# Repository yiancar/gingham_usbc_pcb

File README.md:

Gingham-USBC
================

This ANSI/ISO keyboard kit is made using ONLY through hole components and inspired by the [Plaid](https://github.com/hsgw/plaid).

Atmega328p with VUSB on [QMK firmware](https://github.com/qmk/qmk_firmware).

To alter the pcb use KiCAD V5.0 or newer as it already contains most of the libraries. The additional libraries are provided.

License
===========

This project is licensed under the [Creative Commons Attribution-NonCommercial 4.0 International License](https://creativecommons.org/licenses/by-nc/4.0/).

If you have remixed, adapted or build upon this work and wish to remove the non-commercial clause for your own project please contact me at https://www.yiancar-designs.com. Your request is more than likely to be granted. The non-commercial part of the license is intended to avoid direct copies of the work to be sold for commercial gain by third parties.

The USB4085-GF-A footprint, symbol and 3D model are licensed under [Attribution-ShareAlike 4.0 International](https://creativecommons.org/licenses/by-sa/4.0/). Originally created by [SnapEDA](https://snapeda.com). The footprint has been modified to increase the hole size of the shield pads.

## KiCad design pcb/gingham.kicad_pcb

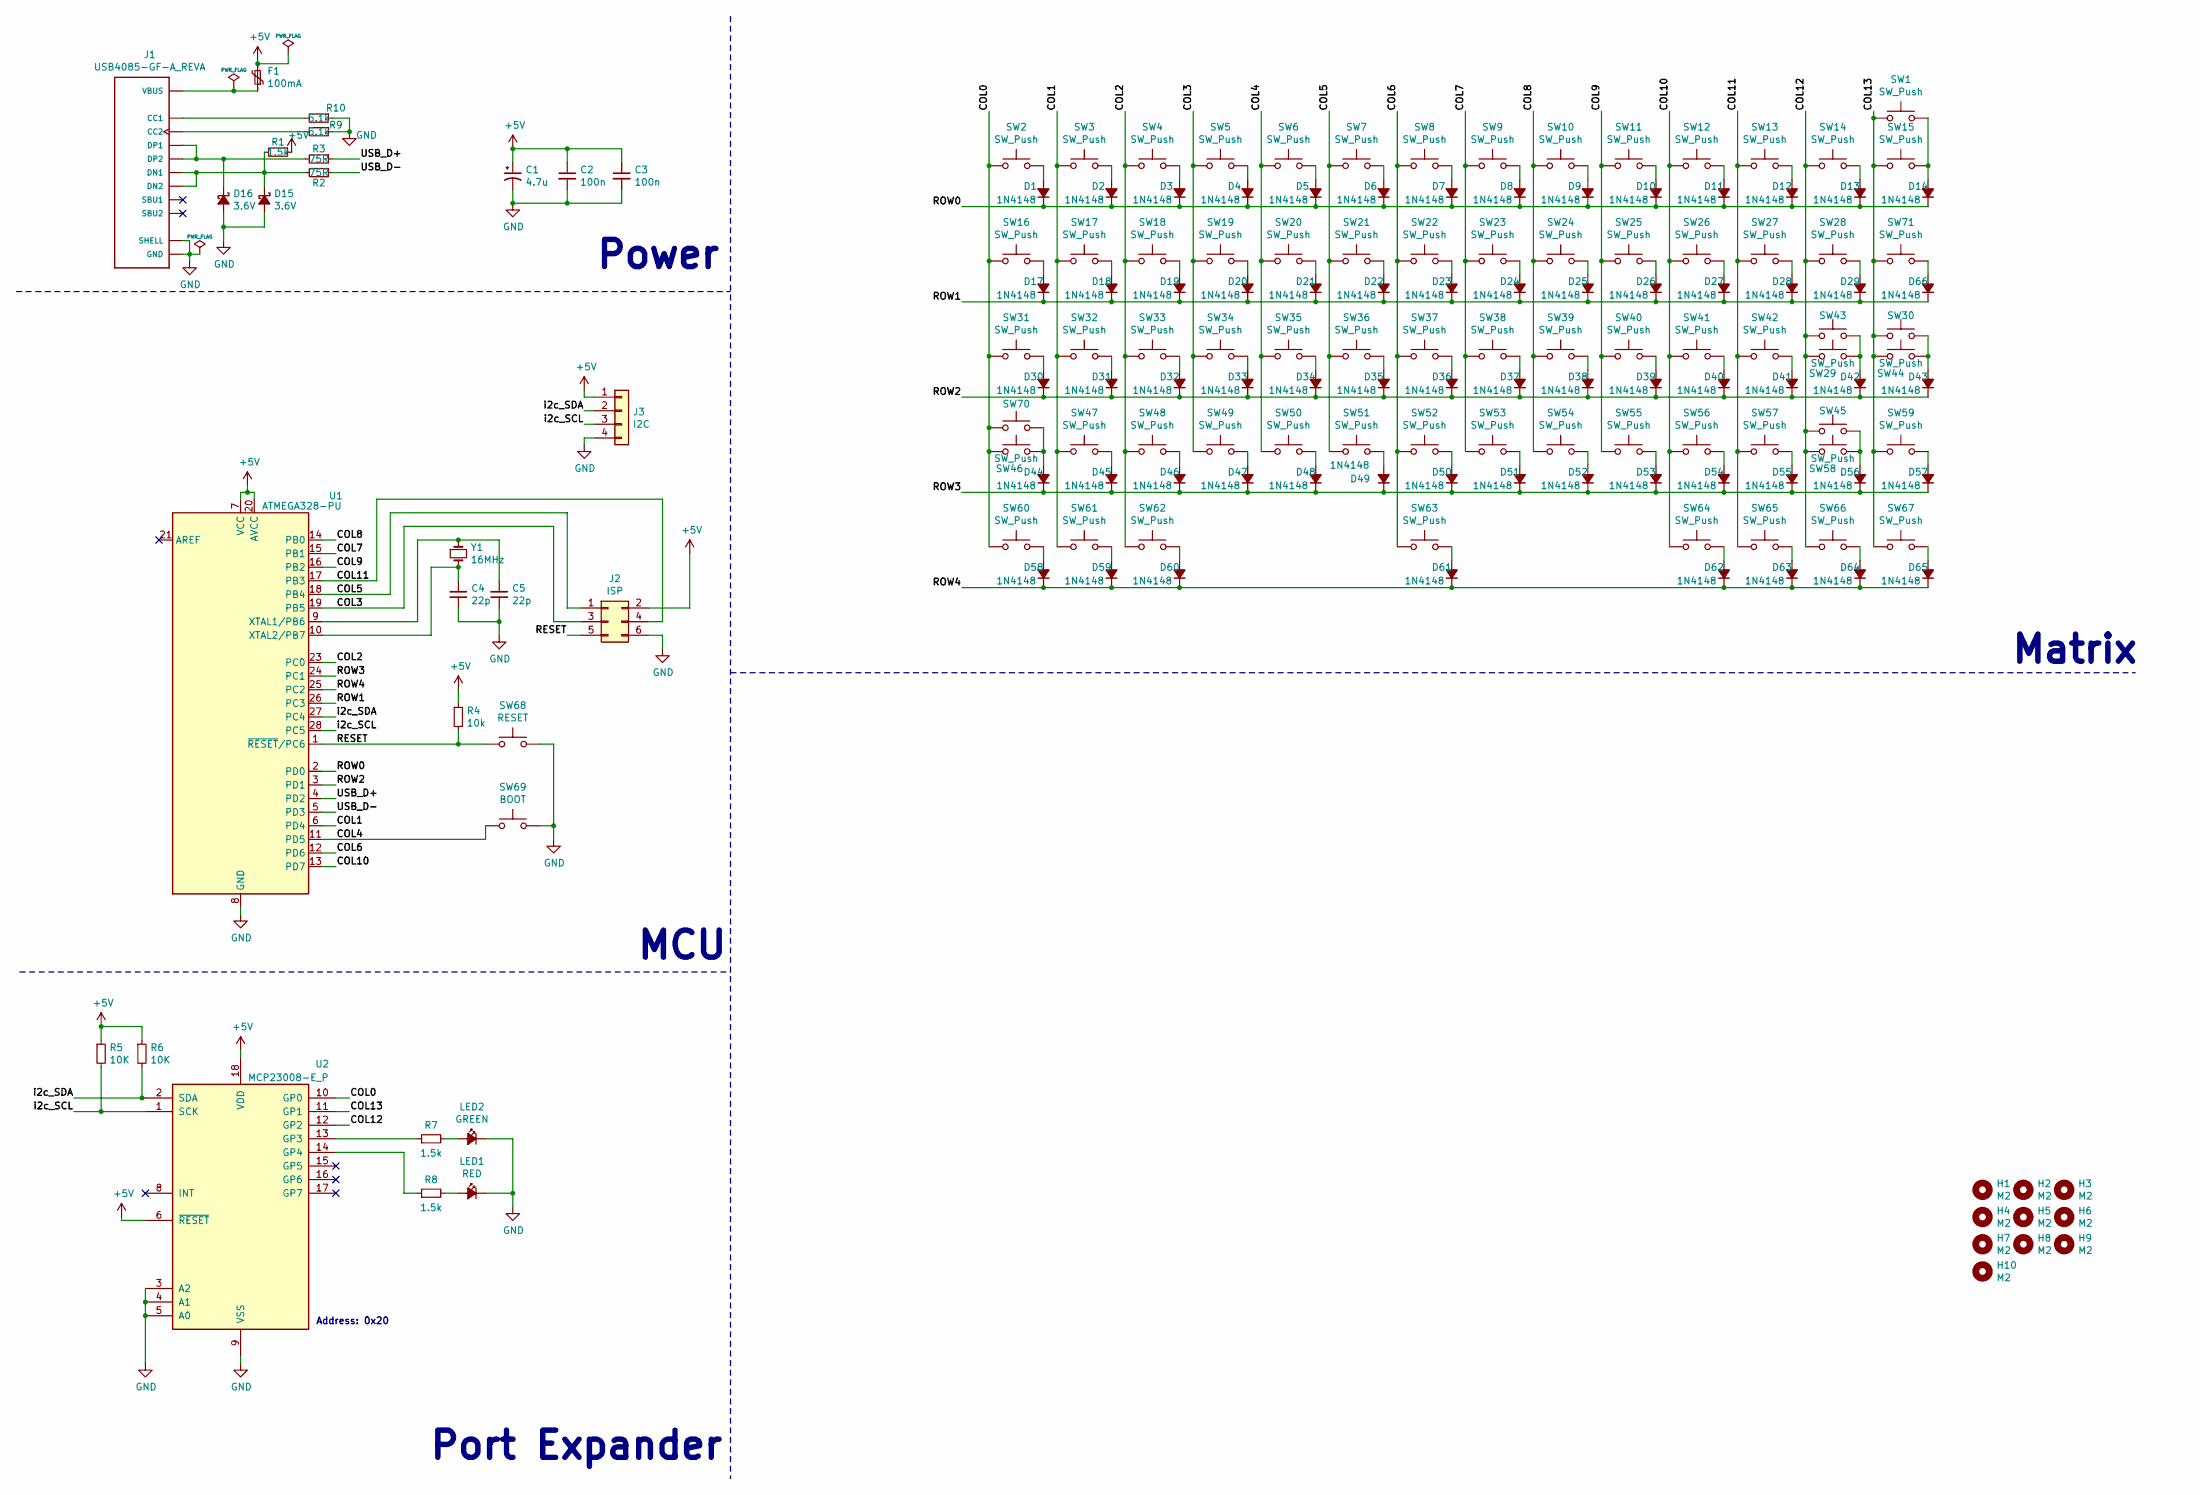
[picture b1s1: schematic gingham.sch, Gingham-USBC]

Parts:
C1: 4.7u; CP_Radial_D4.0mm_P1.50mm
C2, C3: 100n; C_Disc_D4.3mm_W1.9mm_P5.00mm
C4, C5: 22p; C_Disc_D4.3mm_W1.9mm_P5.00mm
D1, D2, D3, D4, D5, D6, D7, D8, D9, D10, D11, D12, D13, D14, D17, D18, D19, D20, D21, D22, D23, D24, D25, D26, D27, D28, D29, D30, D31, D32, D33, D34, D35, D36, D37, D38, D39, D40, D41, D42, D43, D44, D45, D46, D47, D48, D49, D50, D51, D52, D53, D54, D55, D56, D57, D58, D59, D60, D61, D62, D63, D64, D65, D66: 1N4148; D_DO-35_SOD27_P7.62mm_Horizontal
D15, D16: 3.6V; D_DO-35_SOD27_P7.62mm_Horizontal
F1: 100mA; C_Disc_D5.0mm_W2.5mm_P5.00mm
H1, H2, H3, H4, H5, H6, H7, H8, H9, H10: M2; MountingHole_2.2mm_M2_DIN965_Pad
J1: USB4085-GF-A_REVA; GCT_USB4085-GF-A_REVA
J2: ISP; PinHeader_2x03_P2.54mm_Vertical
J3: I2C; PinHeader_1x04_P2.54mm_Vertical
LED1: RED; LED_D3.0mm_Clear
LED2: GREEN; LED_D3.0mm_Clear
R1, R7, R8: 1.5k; R_Axial_DIN0204_L3.6mm_D1.6mm_P5.08mm_Horizontal
R2, R3: 75R; R_Axial_DIN0204_L3.6mm_D1.6mm_P5.08mm_Horizontal
R4: 10k; R_Axial_DIN0204_L3.6mm_D1.6mm_P5.08mm_Horizontal
R5, R6: 10K; R_Axial_DIN0204_L3.6mm_D1.6mm_P5.08mm_Horizontal
R9, R10: 5.1k; R_Axial_DIN0204_L3.6mm_D1.6mm_P5.08mm_Horizontal
SW1: SW_Push; MX-2U-NoLED
SW2, SW3, SW4, SW5, SW6, SW7, SW8, SW9, SW10, SW11, SW12, SW13, SW14, SW15, SW17, SW18, SW19, SW20, SW21, SW22, SW23, SW24, SW25, SW26, SW27, SW28, SW29, SW32, SW33, SW34, SW35, SW36, SW37, SW38, SW39, SW40, SW41, SW42, SW47, SW48, SW49, SW50, SW51, SW52, SW53, SW54, SW55, SW56, SW57, SW59, SW71: SW_Push; MX-1U-NoLED
SW16, SW43: SW_Push; MX-1.5U-NoLED
SW30: SW_Push; MX-ISO-ReversedStabilizers
SW31, SW45: SW_Push; MX-1.75U-NoLED
SW44, SW46: SW_Push; MX-2.25U-NoLED
SW58: SW_Push; MX-2.75U-NoLED
SW60, SW61, SW62, SW64, SW65, SW66, SW67, SW70: SW_Push; MX-1.25U-NoLED
SW63: SW_Push; MX-6.25U-ReversedStabilizers-NoLED
SW68: RESET; SW_PUSH_6mm
SW69: BOOT; SW_PUSH_6mm
U1: ATMEGA328-PU; DIP-28_W7.62mm
U2: MCP23008-E_P; DIP-18_W7.62mm
Y1: 16MHz; Crystal_HC49-4H_Vertical

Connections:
+5V: C1.1, C2.1, C3.1, F1.2, J2.2, J3.1, R1.1, R4.1, R5.1, R6.1, U1.7 (VCC), U1.20 (AVCC), U2.6 (~RESET~), U2.18 (VDD)
/COL0: SW2.2, SW16.2, SW31.2, SW46.2, SW60.2, SW70.2, U2.10 (GP0)
/COL1: SW3.2, SW17.2, SW32.2, SW47.2, SW61.2, U1.6 (PD4)
/COL2: SW4.2, SW18.2, SW33.2, SW48.2, SW62.2, U1.23 (PC0)
/COL3: J2.3, SW5.2, SW19.2, SW34.2, SW49.2, U1.19 (PB5)
/COL4: SW6.2, SW20.2, SW35.2, SW50.2, SW69.1, U1.11 (PD5)
/COL5: J2.1, SW7.2, SW21.2, SW36.2, SW51.2, U1.18 (PB4)
/COL6: SW8.2, SW22.2, SW37.2, SW52.2, SW63.2, U1.12 (PD6)
/COL7: SW9.2, SW23.2, SW38.2, SW53.2, U1.15 (PB1)
/COL8: SW10.2, SW24.2, SW39.2, SW54.2, U1.14 (PB0)
/COL9: SW11.2, SW25.2, SW40.2, SW55.2, U1.16 (PB2)
/COL10: SW12.2, SW26.2, SW41.2, SW56.2, SW64.2, U1.13 (PD7)
/COL11: J2.4, SW13.2, SW27.2, SW42.2, SW57.2, SW65.2, U1.17 (PB3)
/COL12: SW14.2, SW28.2, SW29.2, SW43.2, SW45.2, SW58.2, SW66.2, U2.12 (GP2)
/COL13: SW1.2, SW15.2, SW30.2, SW44.2, SW59.2, SW67.2, SW71.2, U2.11 (GP1)
/RESET: J2.5, R4.2, SW68.1, U1.1 (~RESET~/PC6)
/ROW0: D1.1 (K), D2.1 (K), D3.1 (K), D4.1 (K), D5.1 (K), D6.1 (K), D7.1 (K), D8.1 (K), D9.1 (K), D10.1 (K), D11.1 (K), D12.1 (K), D13.1 (K), D14.1 (K), U1.2 (PD0)
/ROW1: D17.1 (K), D18.1 (K), D19.1 (K), D20.1 (K), D21.1 (K), D22.1 (K), D23.1 (K), D24.1 (K), D25.1 (K), D26.1 (K), D27.1 (K), D28.1 (K), D29.1 (K), D66.1 (K), U1.26 (PC3)
/ROW2: D30.1 (K), D31.1 (K), D32.1 (K), D33.1 (K), D34.1 (K), D35.1 (K), D36.1 (K), D37.1 (K), D38.1 (K), D39.1 (K), D40.1 (K), D41.1 (K), D42.1 (K), D43.1 (K), U1.3 (PD1)
/ROW3: D44.1 (K), D45.1 (K), D46.1 (K), D47.1 (K), D48.1 (K), D49.1 (K), D50.1 (K), D51.1 (K), D52.1 (K), D53.1 (K), D54.1 (K), D55.1 (K), D56.1 (K), D57.1 (K), U1.24 (PC1)
/ROW4: D58.1 (K), D59.1 (K), D60.1 (K), D61.1 (K), D62.1 (K), D63.1 (K), D64.1 (K), D65.1 (K), U1.25 (PC2)
/USB_D+: R3.1, U1.4 (PD2)
/USB_D-: R2.1, U1.5 (PD3)
/i2c_SCL: J3.3, R5.2, U1.28 (PC5), U2.1 (SCK)
/i2c_SDA: J3.2, R6.2, U1.27 (PC4), U2.2 (SDA)
GND: C1.2, C2.2, C3.2, C4.2, C5.2, D15.2 (A), D16.2 (A), J1.A1 (GND), J1.A12 (GND), J1.B1 (GND), J1.B12 (GND), J1.P1 (SHELL), J1.P2 (SHELL), J1.P3 (SHELL), J1.P4 (SHELL), J2.6, J3.4, LED1.1 (K), LED2.1 (K), R9.1, R10.1, SW68.2, SW69.2, U1.8 (GND), U1.22 (GND), U2.3 (A2), U2.4 (A1), U2.5 (A0), U2.9 (VSS)
unnamed: C4.1, U1.10 (XTAL2/PB7), Y1.2
unnamed: C5.1, U1.9 (XTAL1/PB6), Y1.1
unnamed: D1.2 (A), SW2.1
unnamed: D2.2 (A), SW3.1
unnamed: D3.2 (A), SW4.1
unnamed: D4.2 (A), SW5.1
unnamed: D5.2 (A), SW6.1
unnamed: D6.2 (A), SW7.1
unnamed: D7.2 (A), SW8.1
unnamed: D8.2 (A), SW9.1
unnamed: D9.2 (A), SW10.1
unnamed: D10.2 (A), SW11.1
unnamed: D11.2 (A), SW12.1
unnamed: D12.2 (A), SW13.1
unnamed: D13.2 (A), SW14.1
unnamed: D14.2 (A), SW1.1, SW15.1
unnamed: D15.1 (K), J1.A7 (DN1), J1.B7 (DN2), R1.2, R2.2
unnamed: D16.1 (K), J1.A6 (DP1), J1.B6 (DP2), R3.2
unnamed: D17.2 (A), SW16.1
unnamed: D18.2 (A), SW17.1
unnamed: D19.2 (A), SW18.1
unnamed: D20.2 (A), SW19.1
unnamed: D21.2 (A), SW20.1
unnamed: D22.2 (A), SW21.1
unnamed: D23.2 (A), SW22.1
unnamed: D24.2 (A), SW23.1
unnamed: D25.2 (A), SW24.1
unnamed: D26.2 (A), SW25.1
unnamed: D27.2 (A), SW26.1
unnamed: D28.2 (A), SW27.1
unnamed: D29.2 (A), SW28.1
unnamed: D30.2 (A), SW31.1
unnamed: D31.2 (A), SW32.1
unnamed: D32.2 (A), SW33.1
unnamed: D33.2 (A), SW34.1
unnamed: D34.2 (A), SW35.1
unnamed: D35.2 (A), SW36.1
unnamed: D36.2 (A), SW37.1
unnamed: D37.2 (A), SW38.1
unnamed: D38.2 (A), SW39.1
unnamed: D39.2 (A), SW40.1
unnamed: D40.2 (A), SW41.1
unnamed: D41.2 (A), SW42.1
unnamed: D42.2 (A), SW29.1, SW43.1
unnamed: D43.2 (A), SW30.1, SW44.1
unnamed: D44.2 (A), SW46.1, SW70.1
unnamed: D45.2 (A), SW47.1
unnamed: D46.2 (A), SW48.1
unnamed: D47.2 (A), SW49.1
unnamed: D48.2 (A), SW50.1
unnamed: D49.2 (A), SW51.1
unnamed: D50.2 (A), SW52.1
unnamed: D51.2 (A), SW53.1
unnamed: D52.2 (A), SW54.1
unnamed: D53.2 (A), SW55.1
unnamed: D54.2 (A), SW56.1
unnamed: D55.2 (A), SW57.1
unnamed: D56.2 (A), SW45.1, SW58.1
unnamed: D57.2 (A), SW59.1
unnamed: D58.2 (A), SW60.1
unnamed: D59.2 (A), SW61.1
unnamed: D60.2 (A), SW62.1
unnamed: D61.2 (A), SW63.1
unnamed: D62.2 (A), SW64.1
unnamed: D63.2 (A), SW65.1
unnamed: D64.2 (A), SW66.1
unnamed: D65.2 (A), SW67.1
unnamed: D66.2 (A), SW71.1
unnamed: F1.1, J1.A4 (VBUS), J1.A9 (VBUS), J1.B4 (VBUS), J1.B9 (VBUS)
unnamed: J1.A5 (CC1), R10.2
unnamed: J1.B5 (CC2), R9.2
unnamed: LED1.2 (A), R8.2
unnamed: LED2.2 (A), R7.2
unnamed: R7.1, U2.13 (GP3)
unnamed: R8.1, U2.14 (GP4)

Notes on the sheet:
Power
Matrix
MCU
Port Expander
Address: 0x20

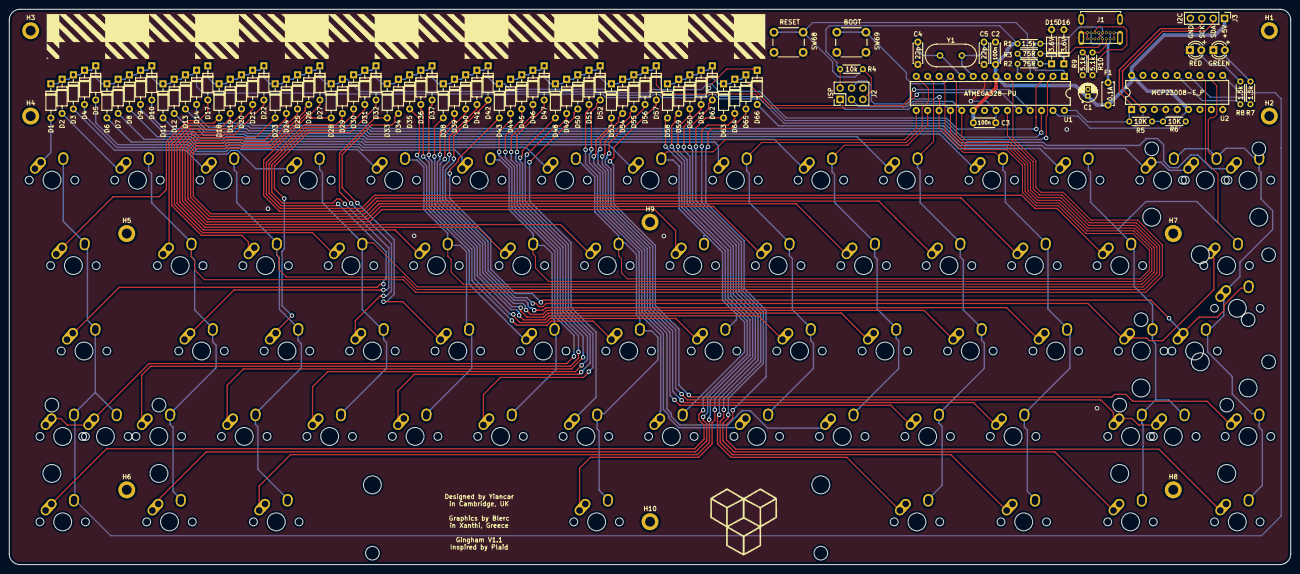
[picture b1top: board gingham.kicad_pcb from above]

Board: 2 copper layers, 285.8 x 123.8 mm, 172 parts (0 on the bottom side), 101 nets.

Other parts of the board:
svg2mod: G***; gingham

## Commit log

2020-06-18 Add files
2020-06-18 add submodules
2020-06-18 Submodules
2020-06-18 Fix submodules
2020-07-19 Update Instructions
2020-07-22 Create fp-info-cache

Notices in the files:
README.md:
cc-by-nc
